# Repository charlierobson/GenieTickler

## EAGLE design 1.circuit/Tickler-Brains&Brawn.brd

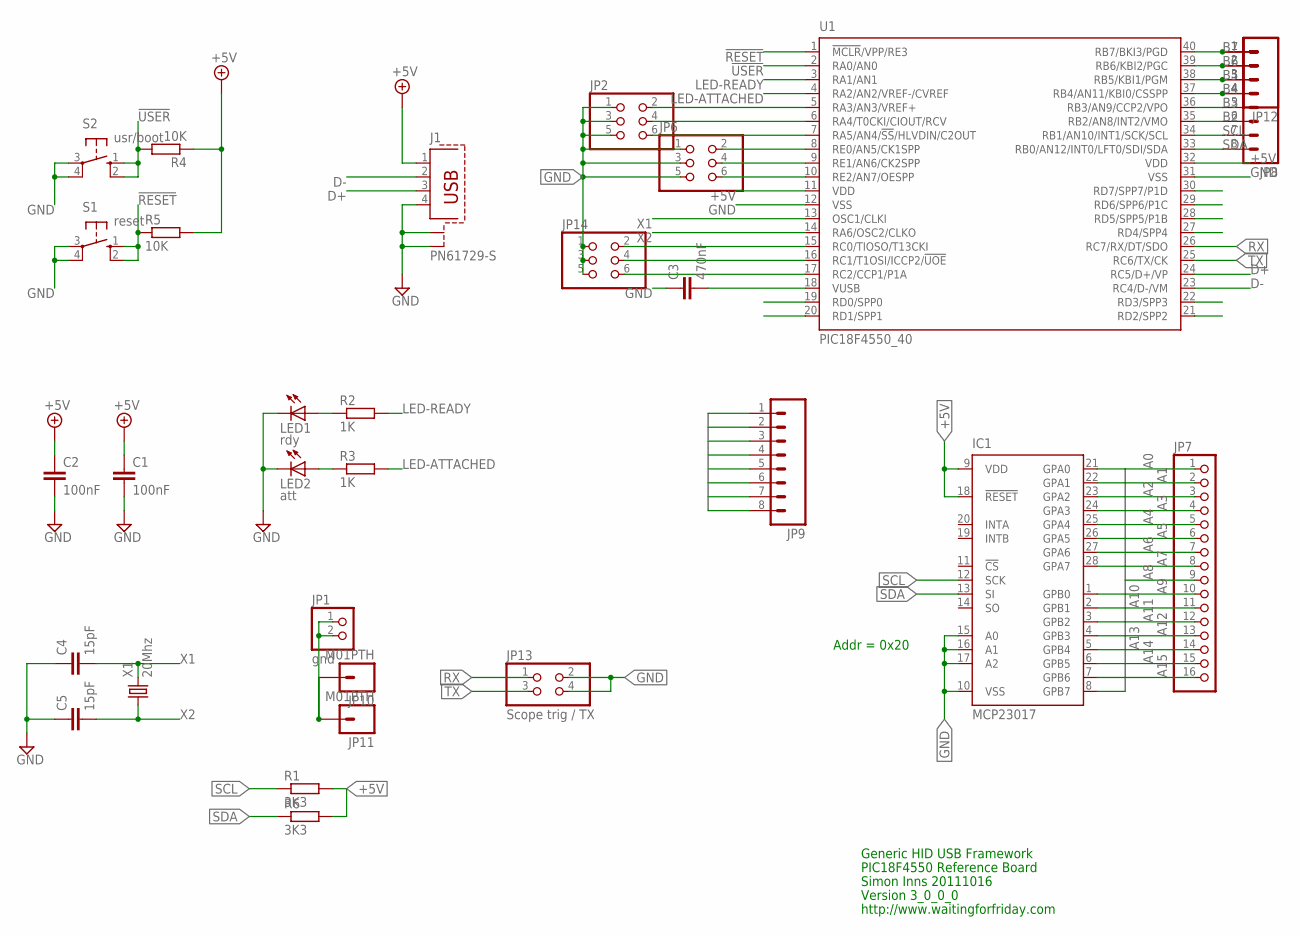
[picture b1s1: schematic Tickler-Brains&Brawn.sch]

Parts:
C1, C2: 100nF; C025-025X050
C3: 470nF; C025-025X050
C4, C5: 15pF; C050-024X044
IC1: MCP23017; DIL28-3
J1: PN61729-S
JP1: gnd; 1X02
JP2, JP6, JP14: PINHD-2X3; 2X03
JP7: PINHD-1X16; 1X16
JP8, JP9: M08; 1X08
JP10, JP11: M01PTH; 1X01
JP12: M04PTH; 1X04
JP13: Scope trig / TX; 2X02
LED1: rdy; LED3MM
LED2: att; LED3MM
R1, R6: 3K3; 0207/10
R2, R3: 1K; 0207/10
R4, R5: 10K; 0207/10
S1: reset; B3F-10XX
S2: usr/boot; B3F-10XX
U1: PIC18F4550_40; DIL40
X1: 20Mhz; HC49U-V

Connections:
!RESET: R5.1, S1.1 (S), S1.2 (S1), U1.1 (!MCLR!/VPP/RE3)
!USER: R4.2, S2.1 (S), S2.2 (S1), U1.2 (RA0/AN0)
+5V: C1.1, C2.1, IC1.9 (VDD), IC1.18 (!RESET), J1.1, R1.2, R4.1, R5.2, R6.2, U1.11 (VDD), U1.32 (VDD)
A0: IC1.8 (GPB7), JP7.1
A1: IC1.21 (GPA0), JP7.2
A2: IC1.7 (GPB6), JP7.3
A3: IC1.22 (GPA1), JP7.4
A4: IC1.6 (GPB5), JP7.5
A5: IC1.23 (GPA2), JP7.6
A6: IC1.5 (GPB4), JP7.7
A7: IC1.24 (GPA3), JP7.8
A8: IC1.4 (GPB3), JP7.9
A9: IC1.25 (GPA4), JP7.10
A10: IC1.3 (GPB2), JP7.11
A11: IC1.26 (GPA5), JP7.12
A12: IC1.2 (GPB1), JP7.13
A13: IC1.27 (GPA6), JP7.14
A14: IC1.1 (GPB0), JP7.15
A15: IC1.28 (GPA7), JP7.16
B2: JP8.6, U1.35 (RB2/AN8/INT2/VMO)
B3: JP8.5, U1.36 (RB3/AN9/CCP2/VPO)
B4: JP8.4, JP12.4, U1.37 (RB4/AN11/KBI0/CSSPP)
B5: JP8.3, JP12.3, U1.38 (RB5/KBI1/PGM)
B6: JP8.2, JP12.2, U1.39 (RB6/KBI2/PGC)
B7: JP8.1, JP12.1, U1.40 (RB7/BKI3/PGD)
D0: JP9.1, U1.19 (RD0/SPP0)
D1: JP9.2, U1.20 (RD1/SPP1)
D2: JP9.3, U1.21 (RD2/SPP2)
D3: JP9.4, U1.22 (RD3/SPP3)
D4: JP9.5, U1.27 (RD4/SPP4)
D5: JP9.6, U1.28 (RD5/SPP5/P1B)
D6: JP9.7, U1.29 (RD6/SPP6/P1C)
D7: JP9.8, U1.30 (RD7/SPP7/P1D)
D+: J1.3, U1.24 (RC5/D+/VP)
D-: J1.2, U1.23 (RC4/D-/VM)
GND: C1.2, C2.2, C3.1, C4.1, C5.1, IC1.10 (VSS), IC1.15 (A0), IC1.16 (A1), IC1.17 (A2), J1.4, J1.S1, J1.S2, JP1.1, JP1.2, JP2.1, JP2.3, JP2.5, JP6.1, JP6.3, JP6.5, JP10.1, JP11.1, JP13.2, JP13.4, JP14.1, JP14.3, JP14.5, LED1.K (C), LED2.K (C), S1.3, S1.4 (P1), S2.3, S2.4 (P1), U1.12 (VSS), U1.31 (VSS)
LED-ATTACHED: R3.2, U1.4 (RA2/AN2/VREF-/CVREF)
LED-READY: R2.2, U1.3 (RA1/AN1)
unnamed: LED1.A, R2.1
unnamed: LED2.A, R3.1
unnamed: C3.2, U1.18 (VUSB)
unnamed: JP6.6, U1.10 (RE2/AN7/OESPP)
unnamed: JP6.4, U1.9 (RE1/AN6/CK2SPP)
unnamed: JP6.2, U1.8 (RE0/AN5/CK1SPP)
unnamed: JP2.6, U1.7 (RA5/AN4/!SS!/HLVDIN/C2OUT)
unnamed: JP2.4, U1.6 (RA4/T0CKI/CIOUT/RCV)
unnamed: JP2.2, U1.5 (RA3/AN3/VREF+)
unnamed: JP14.6, U1.17 (RC2/CCP1/P1A)
unnamed: JP14.4, U1.16 (RC1/T1OSI/ICCP2/!UOE)
unnamed: JP14.2, U1.15 (RC0/TIOSO/T13CKI)
RX: JP13.1, U1.26 (RC7/RX/DT/SDO)
SCL: IC1.12 (SCK), JP8.7, R1.1, U1.34 (RB1/AN10/INT1/SCK/SCL)
SDA: IC1.13 (SI), JP8.8, R6.1, U1.33 (RB0/AN12/INT0/LFT0/SDI/SDA)
TX: JP13.3, U1.25 (RC6/TX/CK)
X1: C4.2, U1.13 (OSC1/CLKI), X1.2
X2: C5.2, U1.14 (RA6/OSC2/CLKO), X1.1

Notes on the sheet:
http://www.waitingforfriday.com
Generic HID USB Framework
PIC18F4550 Reference Board
Simon Inns 20111016
Version 3_0_0_0
Addr = 0x20

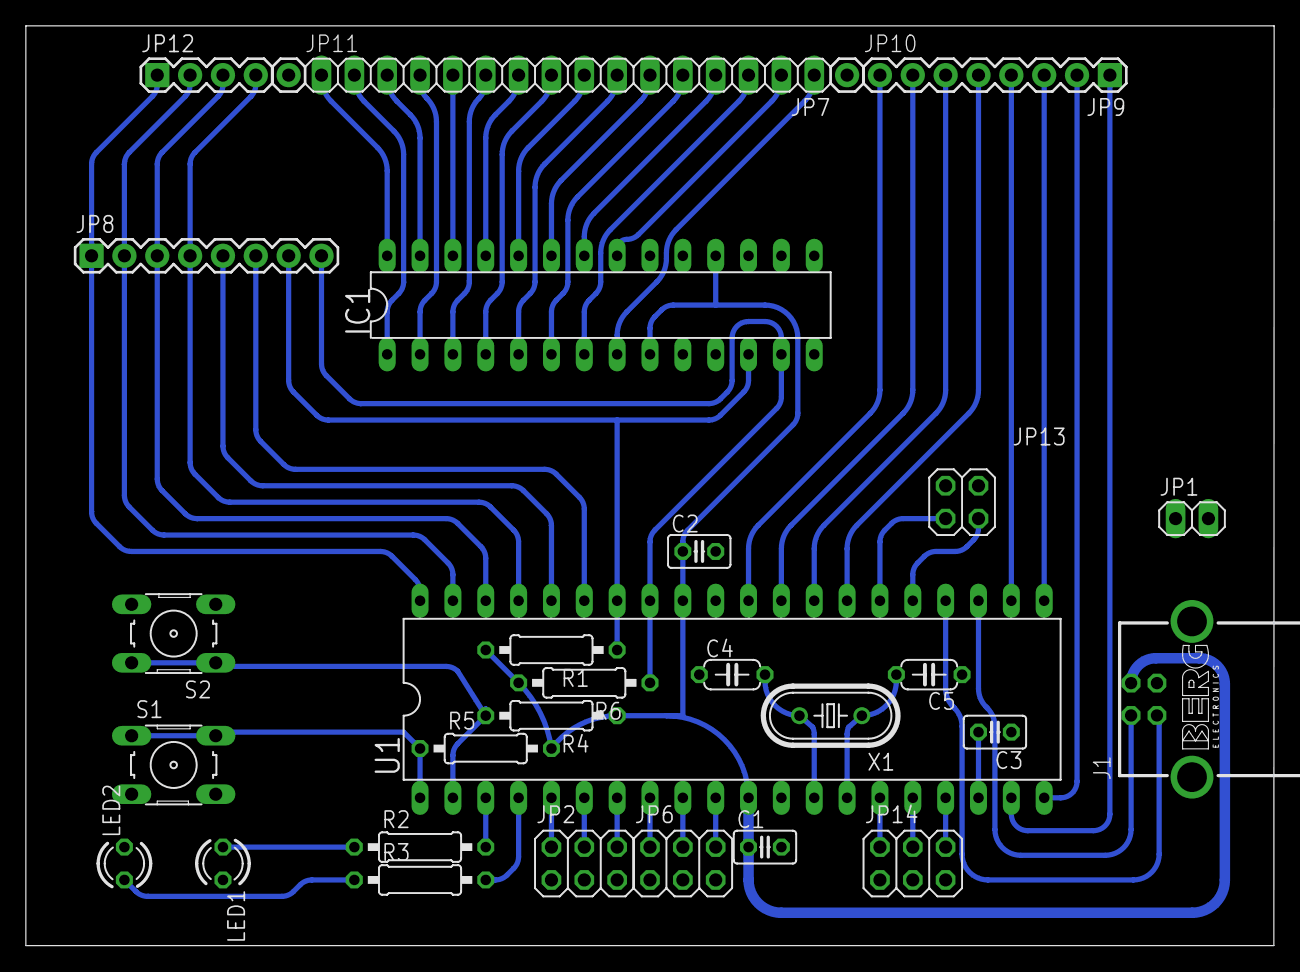
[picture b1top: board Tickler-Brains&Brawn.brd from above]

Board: 2 copper layers, 96.5 x 71.1 mm, 30 parts (0 on the bottom side), 56 nets.

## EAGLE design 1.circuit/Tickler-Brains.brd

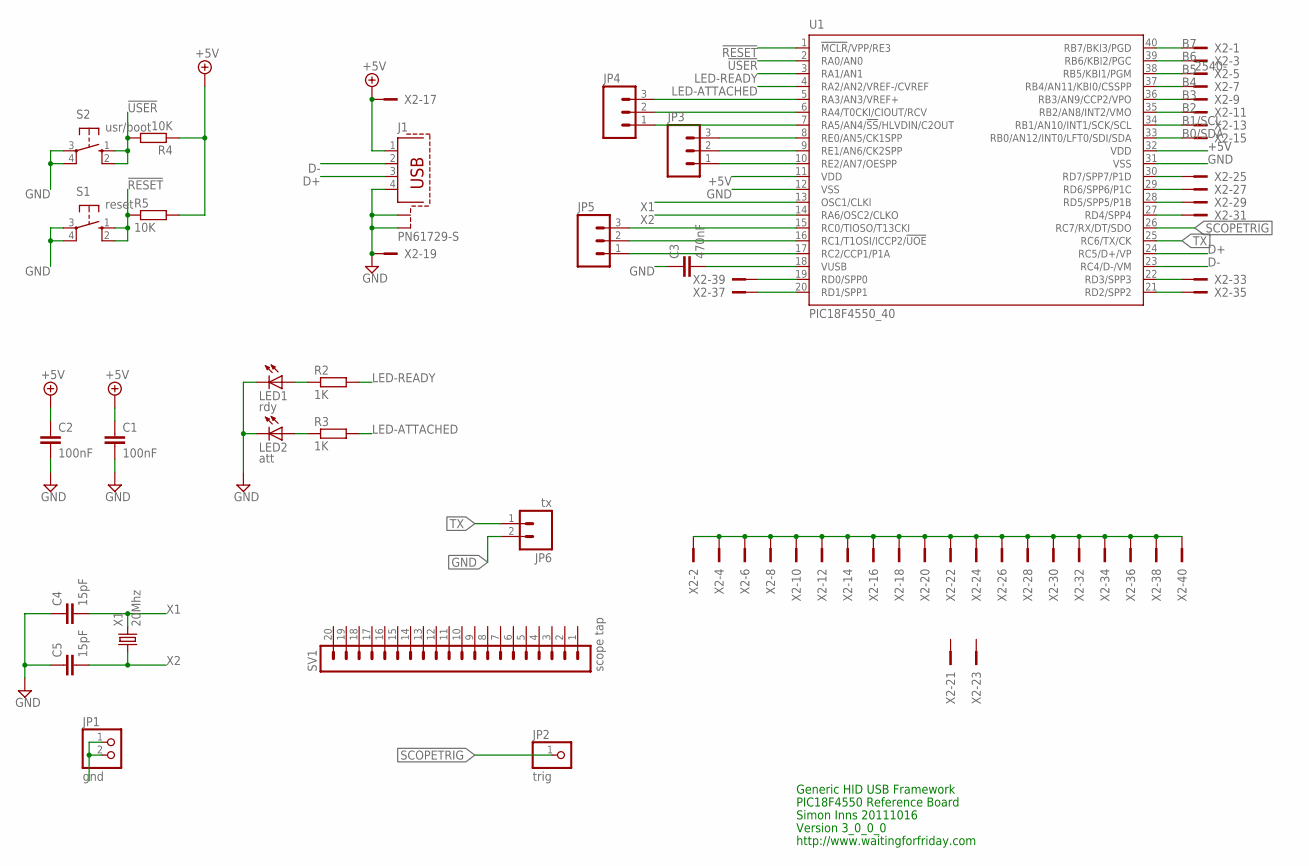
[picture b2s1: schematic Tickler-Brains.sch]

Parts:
C1, C2: 100nF; C025-025X050
C3: 470nF; C025-025X050
C4, C5: 15pF; C050-024X044
J1: PN61729-S
JP1: gnd; 1X02
JP2: trig; 1X01
JP3, JP4, JP5: M03PTH; 1X03
JP6: tx; 1X02
LED1: rdy; LED3MM
LED2: att; LED3MM
R2, R3: 1K; 0207/10
R4, R5: 10K; 0207/10
S1: reset; B3F-10XX
S2: usr/boot; B3F-10XX
SV1: scope tap; MA20-1
U1: PIC18F4550_40; DIL40
X1: 20Mhz; HC49U-V
X2: 2540-; PAK100/2500-40

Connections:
!RESET: R5.1, S1.1 (S), S1.2 (S1), U1.1 (!MCLR!/VPP/RE3)
!USER: R4.2, S2.1 (S), S2.2 (S1), U1.2 (RA0/AN0)
+5V: C1.1, C2.1, J1.1, R4.1, R5.2, U1.11 (VDD), U1.32 (VDD), X2.17
B0/SDA: U1.33 (RB0/AN12/INT0/LFT0/SDI/SDA), X2.15
B1/SCL: U1.34 (RB1/AN10/INT1/SCK/SCL), X2.13
B2: U1.35 (RB2/AN8/INT2/VMO), X2.11
B3: U1.36 (RB3/AN9/CCP2/VPO), X2.9
B4: U1.37 (RB4/AN11/KBI0/CSSPP), X2.7
B5: U1.38 (RB5/KBI1/PGM), X2.5
B6: U1.39 (RB6/KBI2/PGC), X2.3
B7: U1.40 (RB7/BKI3/PGD), X2.1
D+: J1.3, U1.24 (RC5/D+/VP)
D-: J1.2, U1.23 (RC4/D-/VM)
GND: C1.2, C2.2, C3.1, C4.1, C5.1, J1.4, J1.S1, J1.S2, JP1.1, JP1.2, JP6.2, LED1.K (C), LED2.K (C), S1.3, S1.4 (P1), S2.3, S2.4 (P1), U1.12 (VSS), U1.31 (VSS), X2.2, X2.4, X2.6, X2.8, X2.10, X2.12, X2.14, X2.16, X2.18, X2.19, X2.20, X2.22, X2.24, X2.26, X2.28, X2.30, X2.32, X2.34, X2.36, X2.38, X2.40
LED-ATTACHED: R3.2, U1.4 (RA2/AN2/VREF-/CVREF)
LED-READY: R2.2, U1.3 (RA1/AN1)
unnamed: U1.19 (RD0/SPP0), X2.39
unnamed: LED1.A, R2.1
unnamed: LED2.A, R3.1
unnamed: U1.20 (RD1/SPP1), X2.37
unnamed: U1.30 (RD7/SPP7/P1D), X2.25
unnamed: U1.29 (RD6/SPP6/P1C), X2.27
unnamed: U1.28 (RD5/SPP5/P1B), X2.29
unnamed: U1.27 (RD4/SPP4), X2.31
unnamed: U1.22 (RD3/SPP3), X2.33
unnamed: U1.21 (RD2/SPP2), X2.35
unnamed: C3.2, U1.18 (VUSB)
unnamed: JP3.1, U1.10 (RE2/AN7/OESPP)
unnamed: JP3.2, U1.9 (RE1/AN6/CK2SPP)
unnamed: JP3.3, U1.8 (RE0/AN5/CK1SPP)
unnamed: JP4.1, U1.7 (RA5/AN4/!SS!/HLVDIN/C2OUT)
unnamed: JP4.2, U1.6 (RA4/T0CKI/CIOUT/RCV)
unnamed: JP4.3, U1.5 (RA3/AN3/VREF+)
unnamed: JP5.1, U1.17 (RC2/CCP1/P1A)
unnamed: JP5.2, U1.16 (RC1/T1OSI/ICCP2/!UOE)
unnamed: JP5.3, U1.15 (RC0/TIOSO/T13CKI)
SCOPETRIG: JP2.1, U1.26 (RC7/RX/DT/SDO)
TX: JP6.1, U1.25 (RC6/TX/CK)
X1: C4.2, U1.13 (OSC1/CLKI), X1.2
X2: C5.2, U1.14 (RA6/OSC2/CLKO), X1.1

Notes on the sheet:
http://www.waitingforfriday.com
Generic HID USB Framework
PIC18F4550 Reference Board
Simon Inns 20111016
Version 3_0_0_0

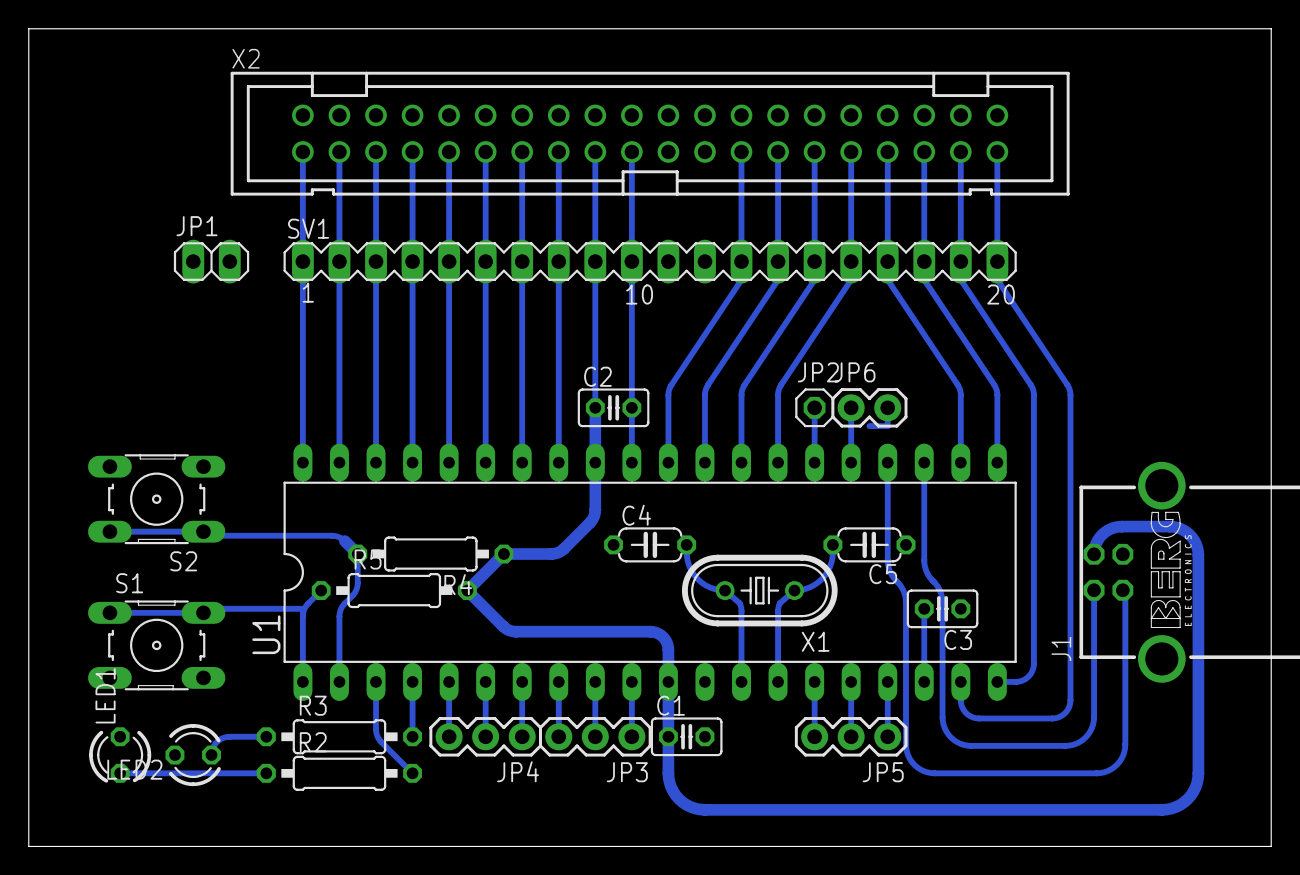
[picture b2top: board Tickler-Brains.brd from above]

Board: 2 copper layers, 86.3 x 56.8 mm, 24 parts (0 on the bottom side), 40 nets.

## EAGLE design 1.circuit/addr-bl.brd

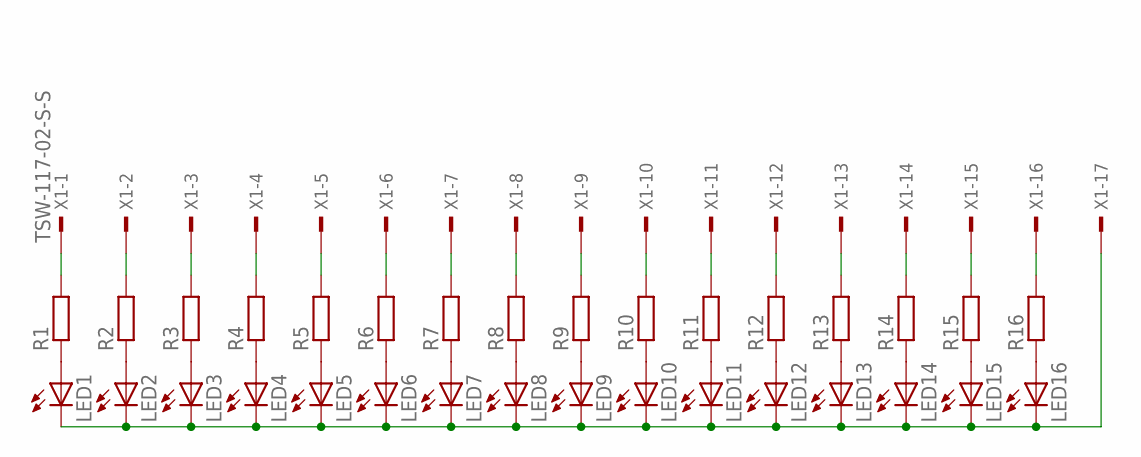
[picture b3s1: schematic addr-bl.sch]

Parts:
LED1, LED2, LED3, LED4, LED5, LED6, LED7, LED8, LED9, LED10, LED11, LED12, LED13, LED14, LED15, LED16: LEDSMT1206; 1206
R1, R2, R3, R4, R5, R6, R7, R8, R9, R10, R11, R12, R13, R14, R15, R16: R-EU_M1206; M1206
X1: TSW-117-02-S-S

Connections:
GND: LED1.C, LED2.C, LED3.C, LED4.C, LED5.C, LED6.C, LED7.C, LED8.C, LED9.C, LED10.C, LED11.C, LED12.C, LED13.C, LED14.C, LED15.C, LED16.C, X1.17
unnamed: LED1.A, R1.1
unnamed: LED2.A, R2.1
unnamed: LED3.A, R3.1
unnamed: LED4.A, R4.1
unnamed: LED5.A, R5.1
unnamed: LED6.A, R6.1
unnamed: LED7.A, R7.1
unnamed: LED8.A, R8.1
unnamed: LED9.A, R9.1
unnamed: LED10.A, R10.1
unnamed: LED11.A, R11.1
unnamed: LED12.A, R12.1
unnamed: LED13.A, R13.1
unnamed: LED14.A, R14.1
unnamed: LED15.A, R15.1
unnamed: LED16.A, R16.1
unnamed: R1.2, X1.1
unnamed: R2.2, X1.2
unnamed: R3.2, X1.3
unnamed: R4.2, X1.4
unnamed: R5.2, X1.5
unnamed: R6.2, X1.6
unnamed: R7.2, X1.7
unnamed: R8.2, X1.8
unnamed: R9.2, X1.9
unnamed: R10.2, X1.10
unnamed: R11.2, X1.11
unnamed: R12.2, X1.12
unnamed: R13.2, X1.13
unnamed: R14.2, X1.14
unnamed: R15.2, X1.15
unnamed: R16.2, X1.16

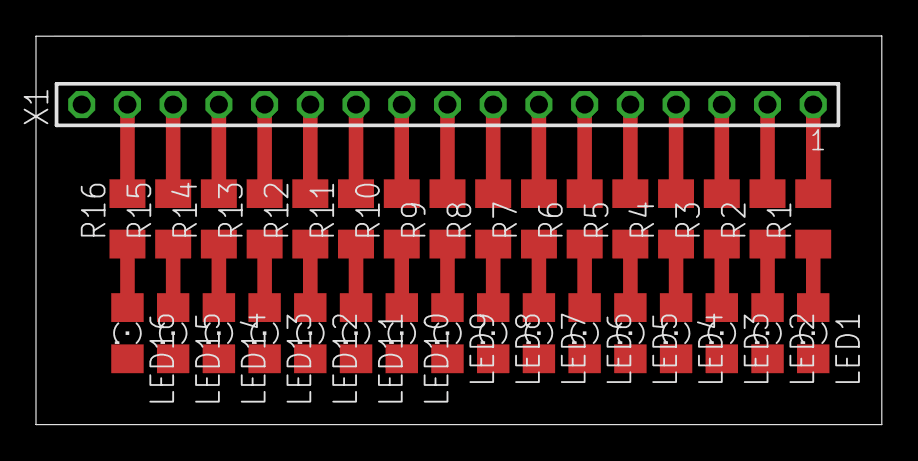
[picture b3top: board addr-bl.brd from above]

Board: 2 copper layers, 47.0 x 21.6 mm, 33 parts (0 on the bottom side), 33 nets.

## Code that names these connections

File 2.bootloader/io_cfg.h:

/*********************************************************************
 *
 *                Microchip USB C18 Firmware 
 *
 *********************************************************************
 * FileName:        io_cfg.h
 * Dependencies:    See INCLUDES section below
 * Processor:       PIC18
 * Compiler:        C18 3.11+
 * Company:         Microchip Technology, Inc.
 *
 * Software License Agreement
 *
 * The software supplied herewith by Microchip Technology Incorporated
 * (the Company) for its PICmicro® Microcontroller is intended and
 * supplied to you, the Companys customer, for use solely and
 * exclusively on Microchip PICmicro Microcontroller products. The
 * software is owned by the Company and/or its supplier, and is
 * protected under applicable copyright laws. All rights are reserved.
 * Any use in violation of the foregoing restrictions may subject the
 * user to criminal sanctions under applicable laws, as well as to
 * civil liability for the breach of the terms and conditions of this
 * license.
 *
 * THIS SOFTWARE IS PROVIDED IN AN AS IS CONDITION. NO WARRANTIES,
 * WHETHER EXPRESS, IMPLIED OR STATUTORY, INCLUDING, BUT NOT LIMITED
 * TO, IMPLIED WARRANTIES OF MERCHANTABILITY AND FITNESS FOR A
 * PARTICULAR PURPOSE APPLY TO THIS SOFTWARE. THE COMPANY SHALL NOT,
 * IN ANY CIRCUMSTANCES, BE LIABLE FOR SPECIAL, INCIDENTAL OR
 * CONSEQUENTIAL DAMAGES, FOR ANY REASON WHATSOEVER.
 *
 * File Version  Date		Comment
 *~~~~~~~~~~~~~~~~~~~~~~~~~~~~~~~~~~~~~~~~~~~~~~~~~~~~~~~~~~~~~~~~~~~~
 * 1.0			 04/09/2008	Started from MCHPFSUSB v1.3 HID Mouse
 *							demo project.  Commented out items that
 *							are not particularly useful for the
 *							bootloader.
 ********************************************************************/

#ifndef IO_CFG_H
#define IO_CFG_H

/** I N C L U D E S *************************************************/
#include "usbcfg.h"

/** T R I S *********************************************************/
#define INPUT_PIN           1
#define OUTPUT_PIN          0

#if defined(PIC18F4550_PICDEM_FS_USB)
/** U S B ***********************************************************/
#define tris_usb_bus_sense  TRISAbits.TRISA1    // Input

#if defined(USE_USB_BUS_SENSE_IO)
#define usb_bus_sense       PORTAbits.RA1
#else
#define usb_bus_sense       1
#endif

#define tris_self_power     TRISAbits.TRISA2    // Input

#if defined(USE_SELF_POWER_SENSE_IO)
#define self_power          PORTAbits.RA2
#else
#define self_power          1
#endif

// External Transceiver Interface
#define tris_usb_vpo        TRISBbits.TRISB3    // Output
#define tris_usb_vmo        TRISBbits.TRISB2    // Output
#define tris_usb_rcv        TRISAbits.TRISA4    // Input
#define tris_usb_vp         TRISCbits.TRISC5    // Input
#define tris_usb_vm         TRISCbits.TRISC4    // Input
#define tris_usb_oe         TRISCbits.TRISC1    // Output

#define tris_usb_suspnd     TRISAbits.TRISA3    // Output

/** L E D ***********************************************************/
#define mInitAllLEDs()      LATD &= 0xF0; TRISD &= 0xF0;

#define mLED_1              LATDbits.LATD0
#define mLED_2              LATDbits.LATD1
#define mLED_3              LATDbits.LATD2
#define mLED_4              LATDbits.LATD3

#define mLED_1_On()         mLED_1 = 1;
#define mLED_2_On()         mLED_2 = 1;
#define mLED_3_On()         mLED_3 = 1;
#define mLED_4_On()         mLED_4 = 1;

#define mLED_1_Off()        mLED_1 = 0;
#define mLED_2_Off()        mLED_2 = 0;
#define mLED_3_Off()        mLED_3 = 0;
#define mLED_4_Off()        mLED_4 = 0;

#define mLED_1_Toggle()     mLED_1 = !mLED_1;
#define mLED_2_Toggle()     mLED_2 = !mLED_2;
#define mLED_3_Toggle()     mLED_3 = !mLED_3;
#define mLED_4_Toggle()     mLED_4 = !mLED_4;

/** S W I T C H *****************************************************/
#define mInitAllSwitches()  TRISBbits.TRISB4=1;TRISBbits.TRISB5=1;
#define mInitSwitch2()      TRISBbits.TRISB4=1;
#define mInitSwitch3()      TRISBbits.TRISB5=1;
#define sw2                 PORTBbits.RB4
#define sw3                 PORTBbits.RB5

/** P O T ***********************************************************/
#define mInitPOT()          TRISAbits.TRISA0=1;ADCON0=0x01;ADCON2=0x3C;

/** S P I : Chip Select Lines ***************************************/
#define tris_cs_temp_sensor TRISBbits.TRISB2    // Output
#define cs_temp_sensor      LATBbits.LATB2

#define tris_cs_sdmmc       TRISBbits.TRISB3    // Output
#define cs_sdmmc            LATBbits.LATB3

/** S D M M C *******************************************************/
#define TRIS_CARD_DETECT    TRISBbits.TRISB4    // Input
#define CARD_DETECT         PORTBbits.RB4

#define TRIS_WRITE_DETECT   TRISAbits.TRISA4    // Input
#define WRITE_DETECT        PORTAbits.RA4

/********************************************************************/
/********************************************************************/
/********************************************************************/



#elif defined(LOW_PIN_COUNT_USB_DEVELOPMENT_KIT)
	//Uncomment the below line(s) if the hardware supports it and
	//it is desireable to use one or both of the features.
	//#define USE_SELF_POWER_SENSE_IO	
	//#define USE_USB_BUS_SENSE_IO

    #define tris_usb_bus_sense  TRISAbits.TRISA1    // Input


	#if defined(USE_USB_BUS_SENSE_IO)
	#define usb_bus_sense       PORTAbits.RA1
	#else
	#define usb_bus_sense       1
	#endif
	
	#define tris_self_power     TRISAbits.TRISA2    // Input
	
	#if defined(USE_SELF_POWER_SENSE_IO)
	#define self_power          PORTAbits.RA2
	#else
	#define self_power          1
	#endif

    
    /** LED ************************************************************/
    #define mInitAllLEDs()      LATC &= 0xF0; TRISC &= 0xF0;
    
    #define mLED_1              LATCbits.LATC0
    #define mLED_2              LATCbits.LATC1
    #define mLED_3              LATCbits.LATC2
    #define mLED_4              LATCbits.LATC3
    
    #define mLED_1_On()         mLED_1 = 1;
    #define mLED_2_On()         mLED_2 = 1;
    #define mLED_3_On()         mLED_3 = 1;
    #define mLED_4_On()         mLED_4 = 1;
    
    #define mLED_1_Off()        mLED_1 = 0;
    #define mLED_2_Off()        mLED_2 = 0;
    #define mLED_3_Off()        mLED_3 = 0;
    #define mLED_4_Off()        mLED_4 = 0;
    
    #define mLED_1_Toggle()     mLED_1 = !mLED_1;
    #define mLED_2_Toggle()     mLED_2 = !mLED_2;
    #define mLED_3_Toggle()     mLED_3 = !mLED_3;
    #define mLED_4_Toggle()     mLED_4 = !mLED_4;
    
    /** SWITCH *********************************************************/
    #define mInitSwitch2()      //TRISAbits.TRISA3=1
        //only one switch available so double duty
    #define mInitSwitch3()      //TRISAbits.TRISA3=1
    #define sw2                 PORTAbits.RA3
    #define sw3                 PORTAbits.RA3
    #define mInitAllSwitches()  mInitSwitch2();
    
    /** POT ************************************************************/
    #define mInitPOT()          {TRISBbits.TRISB4=1;ADCON0=0x29;ADCON1=0;ADCON2=0x3E;ADCON2bits.ADFM = 1;}


#elif defined (SMB_BOARD)

	#define mInitHWSMB() 		LATA = 0; TRISA = 0b11111001;

	#define sw2                 PORTAbits.RA0
    #define mLED_1              LATAbits.LATA1
    #define mLED_2              LATAbits.LATA2

    #define mInitAllSwitches()
    #define mInitAllLEDs()

	#define usb_bus_sense       1
	#define self_power          1

    #define mLED_1_On()         mLED_1 = 1;
    #define mLED_2_On()         mLED_2 = 1;
    
    #define mLED_1_Off()        mLED_1 = 0;
    #define mLED_2_Off()        mLED_2 = 0;

    #define mLED_1_Toggle()     mLED_1 = !mLED_1;
    #define mLED_2_Toggle()     mLED_2 = !mLED_2;


//Uncomment below if using the YOUR_BOARD hardware platform
//#elif defined(YOUR_BOARD)
//Add your hardware specific I/O pin mapping here

#else
    #error Not a supported board (yet), add I/O pin mapping in __FILE__, line __LINE__
#endif

#endif //IO_CFG_H

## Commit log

2016-04-14 first commit of code, let us see how this works out
2016-04-14 some renaming of projects and adjusting include paths
2016-04-14 more renaming - bootloader project this time
2016-04-14 adding basic instructions even though theyre out of date, also link to source site
2016-04-14 why does the bulk fail?
2016-04-15 from home. bugs relating to leds and word reads removed
2016-04-15 adding board, modded schematic
2016-04-15 back to basics, rework from scratch
2016-04-16 some further success - more reliable now but only max 6 bulk sends possible before losing connection. must be the speed of packet sending.
2016-04-16 more reliable still, however 6 or 7 is the most bulk sends that can be achieved
2016-04-17 memory read added, also some hardware initialisation cleanups in the firmware
2016-04-18 adding work functions
2016-04-18 adding scope test points to board
2016-04-18 change how the test buttons on the UI work. test functions are broken
2016-04-18 UI changed up, now for the firmware. continuous processes will run on the pic not be driven by the ui
2016-04-18 board cleanup of labelling etc, headers added for test probing using scope or logic analyser
2016-04-18 ignore file
2016-04-18 adding scope taps and address exerciser business at 0xE2
2016-04-19 ignore
2016-04-19 corrected stupid bug in trigger logic, made the trigger a single pulse rather than square wave and added trigger rate config
2016-04-19 first semblance of drag n drop for the data view
2016-04-19 drag n drop -> data field, data write now sends data to device
2016-04-20 added menu and options for scope trigger style and rate
2016-04-20 moved awkward binary editor into its own class, added initial length selector
2016-04-20 finishing up with the length control
2016-04-21 fixed trigger rate mechanism, added simple button creation for the test pane
2016-04-21 tidy-up and add data byte to constand write
2016-04-22 making shortcuts relative so they work on all dev machines
2016-04-22 change up logging for the worker functions
2016-04-22 changed address exercise business fn to use an offset so the address range stays in range
2016-04-22 re-instate single byte read and write, moving the ui buttons to the action panel. refactor naming of functions in reference device
2016-04-22 app title text updated
2016-04-22 friday noodling, some small tidy up
2016-04-25 adding address and data loop buttons / business
2016-04-25 try out this funky string interpolation lark, moving to c#6
2016-04-27 adding layout suspension to form creation, now using msbuild v14.0 to use c#6 features
2016-04-30 new boards...
2016-05-03 blinkenlight adapter for address lines
2016-05-04 updated pcb to include improvements after building v1 board. software changed to include i2c comms to the expander. not working yet.
2016-05-04 added address bit-munging, untested
2016-05-04 added address twiddling to help test the whiteboard
2016-05-04 stashing
2016-05-04 working! inline asm to mutate the address bits. splendid.
2016-05-04 slight change to board - rx reinstated as its hard to use the usart module with a bifurcated tx and rx pair
2016-05-06 adding fill to the arsenal

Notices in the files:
parts and their libraries:
SparkFun: Licensing: CC v3.0 Share-Alike You are welcome to use this library for commercial purposes.
